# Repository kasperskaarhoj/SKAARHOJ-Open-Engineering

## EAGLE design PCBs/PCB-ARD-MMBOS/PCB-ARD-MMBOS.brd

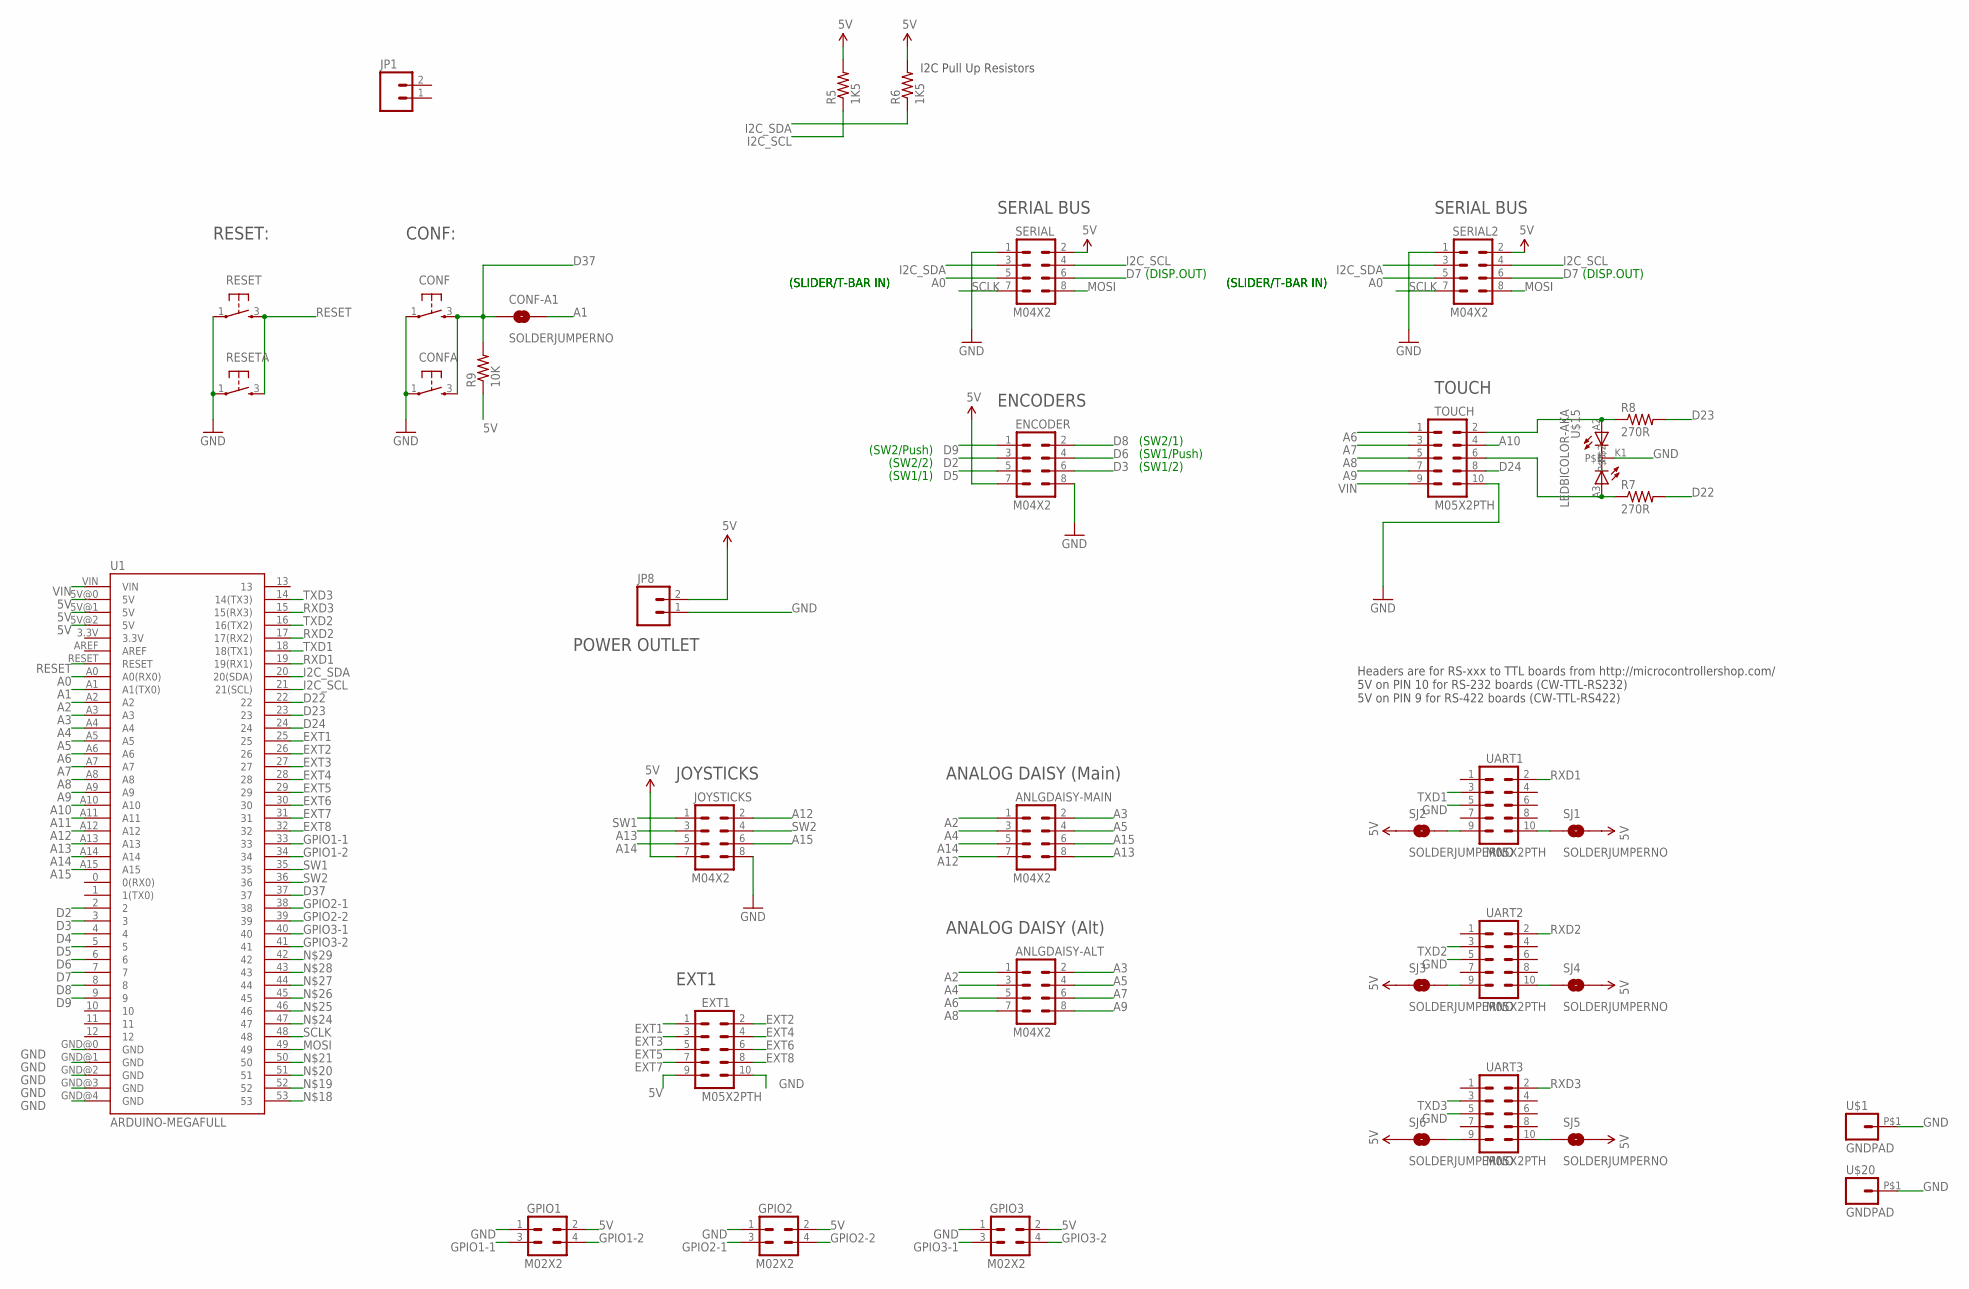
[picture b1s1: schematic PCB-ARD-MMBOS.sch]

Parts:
ANLGDAISY-ALT: M04X2; 2X4
ANLGDAISY-MAIN: M04X2; 2X4
CONF: TAC_SWITCH; PUSHBUTTON
CONF-A1: SOLDERJUMPERNO; SJ_2S-NO
CONFA: TAC_SWITCH; PUSHBUTTON
ENCODER: M04X2; 2X4
EXT1: M05X2PTH; AVR_ICSP
GPIO1, GPIO2, GPIO3: M02X2; 2X2
JOYSTICKS: M04X2; 2X4
JP1: M02PTH; 1X02
JP8: M02PTH4; 1X02_XTRA_BIG
R5, R6: 1K5; 0603-RES
R7, R8: 270R; 0603-RES
R9: 10K; 0603-RES
RESET: TAC_SWITCH; PUSHBUTTON
RESETA: TAC_SWITCH; PUSHBUTTON
SERIAL, SERIAL2: M04X2; 2X4
SJ1, SJ2, SJ3, SJ4, SJ5, SJ6: SOLDERJUMPERNO; SJ_2S-NO
TOUCH: M05X2PTH; AVR_ICSP
U1: ARDUINO-MEGAFULL; ARDUINO_MEGA
U$1, U$20: GNDPAD; 3.2MMPAD
U$15: LEDBICOLOR-AKA; LED5MM-BICOLOR
UART1, UART2, UART3: M05X2PTH; AVR_ICSP

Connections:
5V: ENCODER.7, EXT1.9, GPIO1.2, GPIO2.2, GPIO3.2, JOYSTICKS.7, JP8.2, R5.2, R6.2, R9.1, SERIAL.2, SERIAL2.2, SJ1.2, SJ2.1, SJ3.1, SJ4.2, SJ5.2, SJ6.1, U1.5V@0 (5V), U1.5V@1 (5V), U1.5V@2 (5V)
A0: SERIAL.5, SERIAL2.5, U1.A0 (A0(RX0))
A1: CONF-A1.2, U1.A1 (A1(TX0))
A2: ANLGDAISY-ALT.1, ANLGDAISY-MAIN.1, U1.A2
A3: ANLGDAISY-ALT.2, ANLGDAISY-MAIN.2, U1.A3
A4: ANLGDAISY-ALT.3, ANLGDAISY-MAIN.3, U1.A4
A5: ANLGDAISY-ALT.4, ANLGDAISY-MAIN.4, U1.A5
A6: ANLGDAISY-ALT.5, TOUCH.1, U1.A6
A7: ANLGDAISY-ALT.6, TOUCH.3, U1.A7
A8: ANLGDAISY-ALT.7, TOUCH.5, U1.A8
A9: ANLGDAISY-ALT.8, TOUCH.7, U1.A9
A10: TOUCH.4, U1.A10
A11: U1.A11
A12: ANLGDAISY-MAIN.7, JOYSTICKS.2, U1.A12
A13: ANLGDAISY-MAIN.8, JOYSTICKS.3, U1.A13
A14: ANLGDAISY-MAIN.5, JOYSTICKS.5, U1.A14
A15: ANLGDAISY-MAIN.6, JOYSTICKS.6, U1.A15
D2: ENCODER.3, U1.2
D3: ENCODER.6, U1.3
D4: U1.4
D5: ENCODER.5, U1.5
D6: ENCODER.4, U1.6
D7: SERIAL.6, SERIAL2.6, U1.7
D8: ENCODER.2, U1.8
D9: ENCODER.1, U1.9
D22: R7.2, U1.22
D23: R8.2, U1.23
D24: TOUCH.8, U1.24
D37: CONF.3, CONF-A1.1, CONFA.3, R9.2, U1.37
EXT1: EXT1.1, U1.25
EXT2: EXT1.2, U1.26
EXT3: EXT1.3, U1.27
EXT4: EXT1.4, U1.28
EXT5: EXT1.5, U1.29
EXT6: EXT1.6, U1.30
EXT7: EXT1.7, U1.31
EXT8: EXT1.8, U1.32
GND: CONF.1, CONFA.1, ENCODER.8, EXT1.10, GPIO1.1, GPIO2.1, GPIO3.1, JOYSTICKS.8, JP8.1, RESET.1, RESETA.1, SERIAL.1, SERIAL2.1, TOUCH.10, U1.GND@0 (GND), U1.GND@1 (GND), U1.GND@2 (GND), U1.GND@3 (GND), U1.GND@4 (GND), U$1.P$1, U$15.K1, U$20.P$1, UART1.5, UART2.5, UART3.5
GPIO1-1: GPIO1.3, U1.33
GPIO1-2: GPIO1.4, U1.34
GPIO2-1: GPIO2.3, U1.38
GPIO2-2: GPIO2.4, U1.39
GPIO3-1: GPIO3.3, U1.40
GPIO3-2: GPIO3.4, U1.41
I2C_SCL: R5.1, SERIAL.4, SERIAL2.4, U1.21 (21(SCL))
I2C_SDA: R6.1, SERIAL.3, SERIAL2.3, U1.20 (20(SDA))
MOSI: SERIAL.8, SERIAL2.8, U1.49
unnamed: SJ6.2, UART3.9
unnamed: SJ3.2, UART2.9
unnamed: SJ2.2, UART1.9
unnamed: SJ1.1, UART1.10
unnamed: SJ4.1, UART2.10
unnamed: SJ5.1, UART3.10
unnamed: R8.1, TOUCH.2, U$15.A2
unnamed: R7.1, TOUCH.6, U$15.A3
RESET: RESET.3, RESETA.3, U1.RESET
RXD1: U1.19 (19(RX1)), UART1.2
RXD2: U1.17 (17(RX2)), UART2.2
RXD3: U1.15 (15(RX3)), UART3.2
SCLK: SERIAL.7, SERIAL2.7, U1.48
SW1: JOYSTICKS.1, U1.35
SW2: JOYSTICKS.4, U1.36
TXD1: U1.18 (18(TX1)), UART1.3
TXD2: U1.16 (16(TX2)), UART2.3
TXD3: U1.14 (14(TX3)), UART3.3
VIN: TOUCH.9, U1.VIN

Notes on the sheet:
JOYSTICKS
EXT1
Headers are for RS-xxx to TTL boards from http://microcontrollershop.com/ 5V on PIN 10 for RS-232 boards (CW-TTL-RS232) 5V on PIN 9 for RS-422 boards (CW-TTL-RS422)
I2C Pull Up Resistors
ENCODERS
SERIAL BUS
TOUCH
(SLIDER/T-BAR IN)
(SW2/Push)
(SW2/2)
(SW1/1)
(SW2/1)
(SW1/Push)
(SW1/2)
(DISP.OUT)
RESET:
CONF:
ANALOG DAISY (Main)
ANALOG DAISY (Alt)
POWER OUTLET

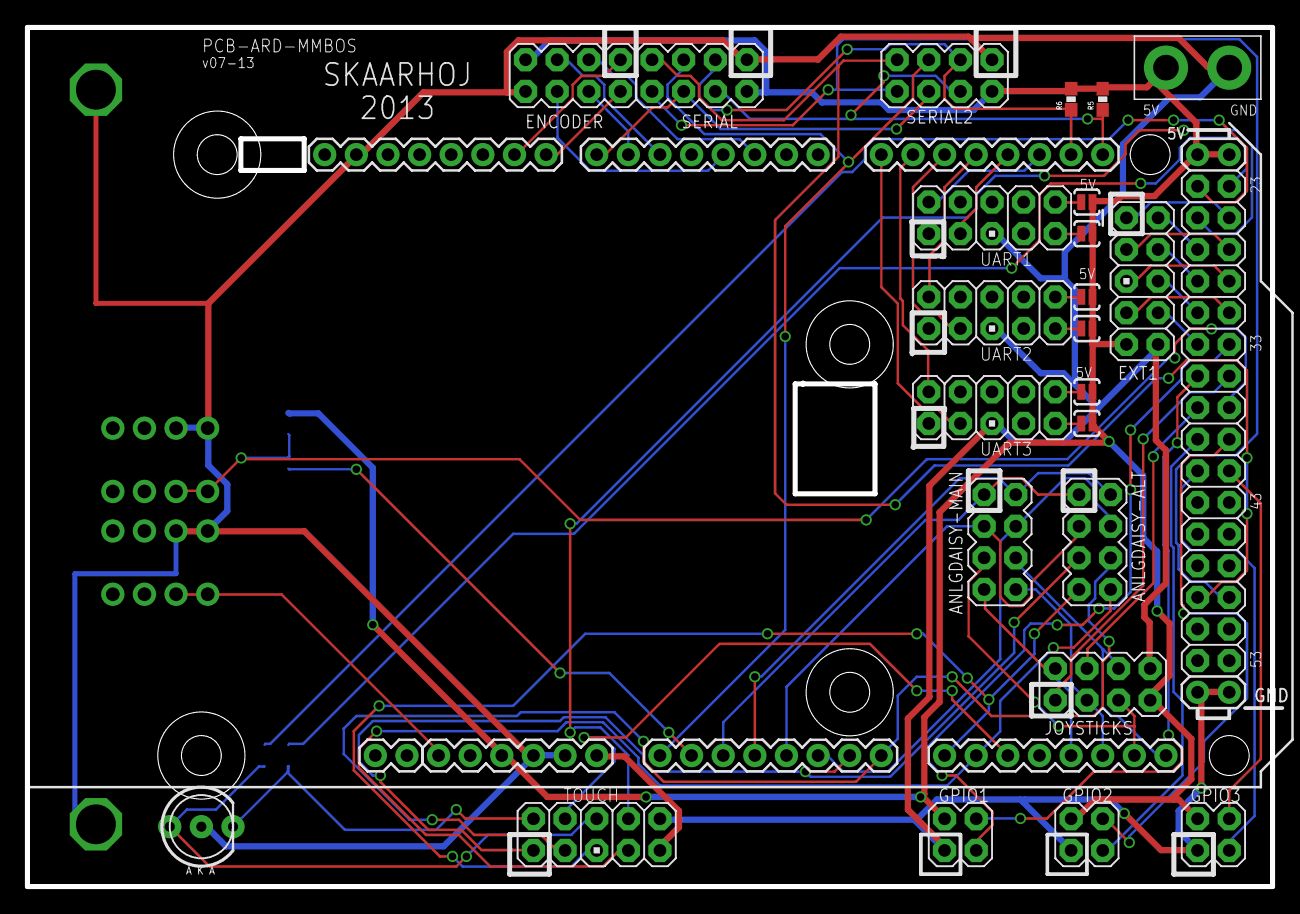
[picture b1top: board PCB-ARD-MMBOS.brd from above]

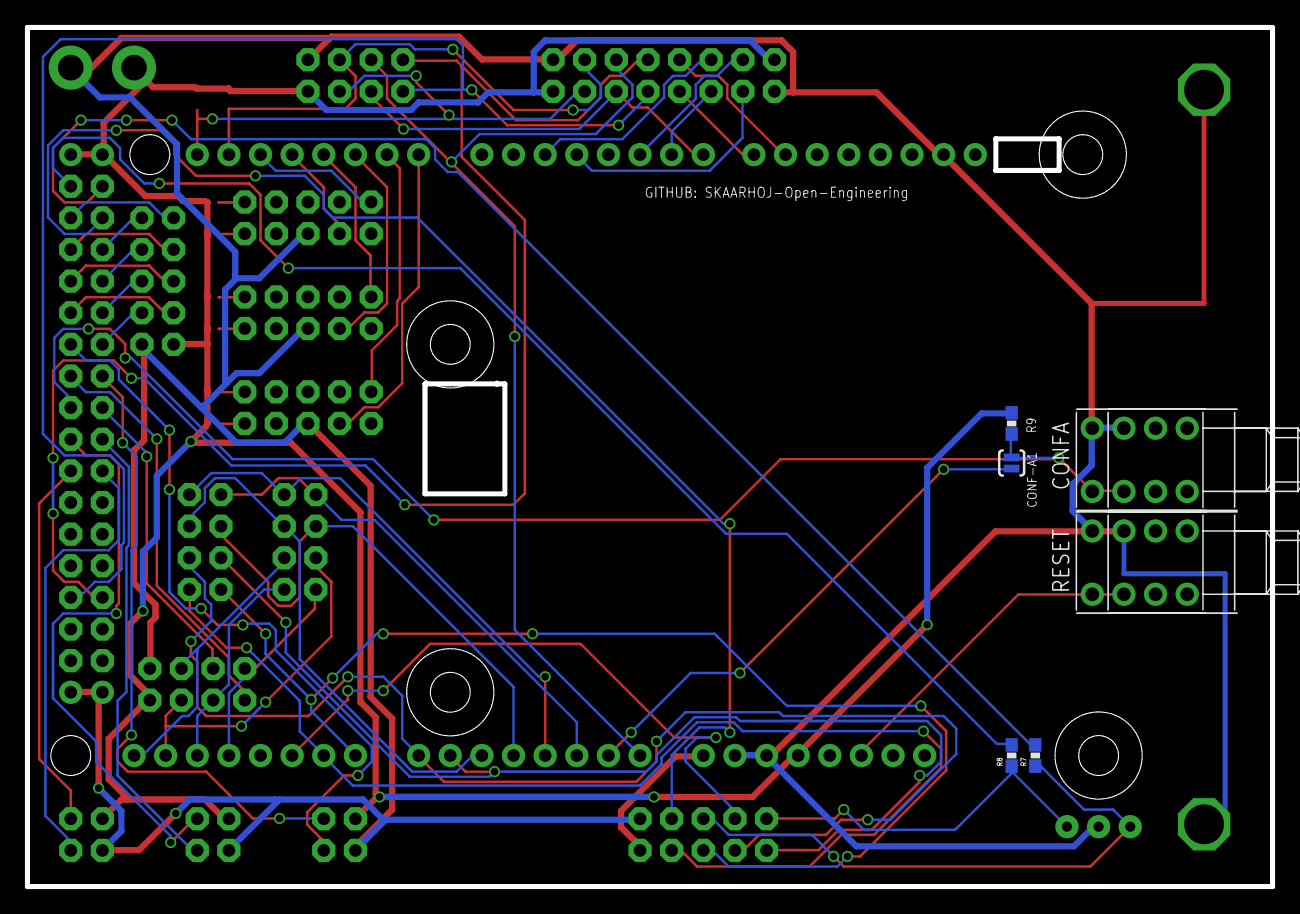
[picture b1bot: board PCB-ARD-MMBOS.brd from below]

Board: 2 copper layers, 100.0 x 69.0 mm, 36 parts (8 on the bottom side), 64 nets.

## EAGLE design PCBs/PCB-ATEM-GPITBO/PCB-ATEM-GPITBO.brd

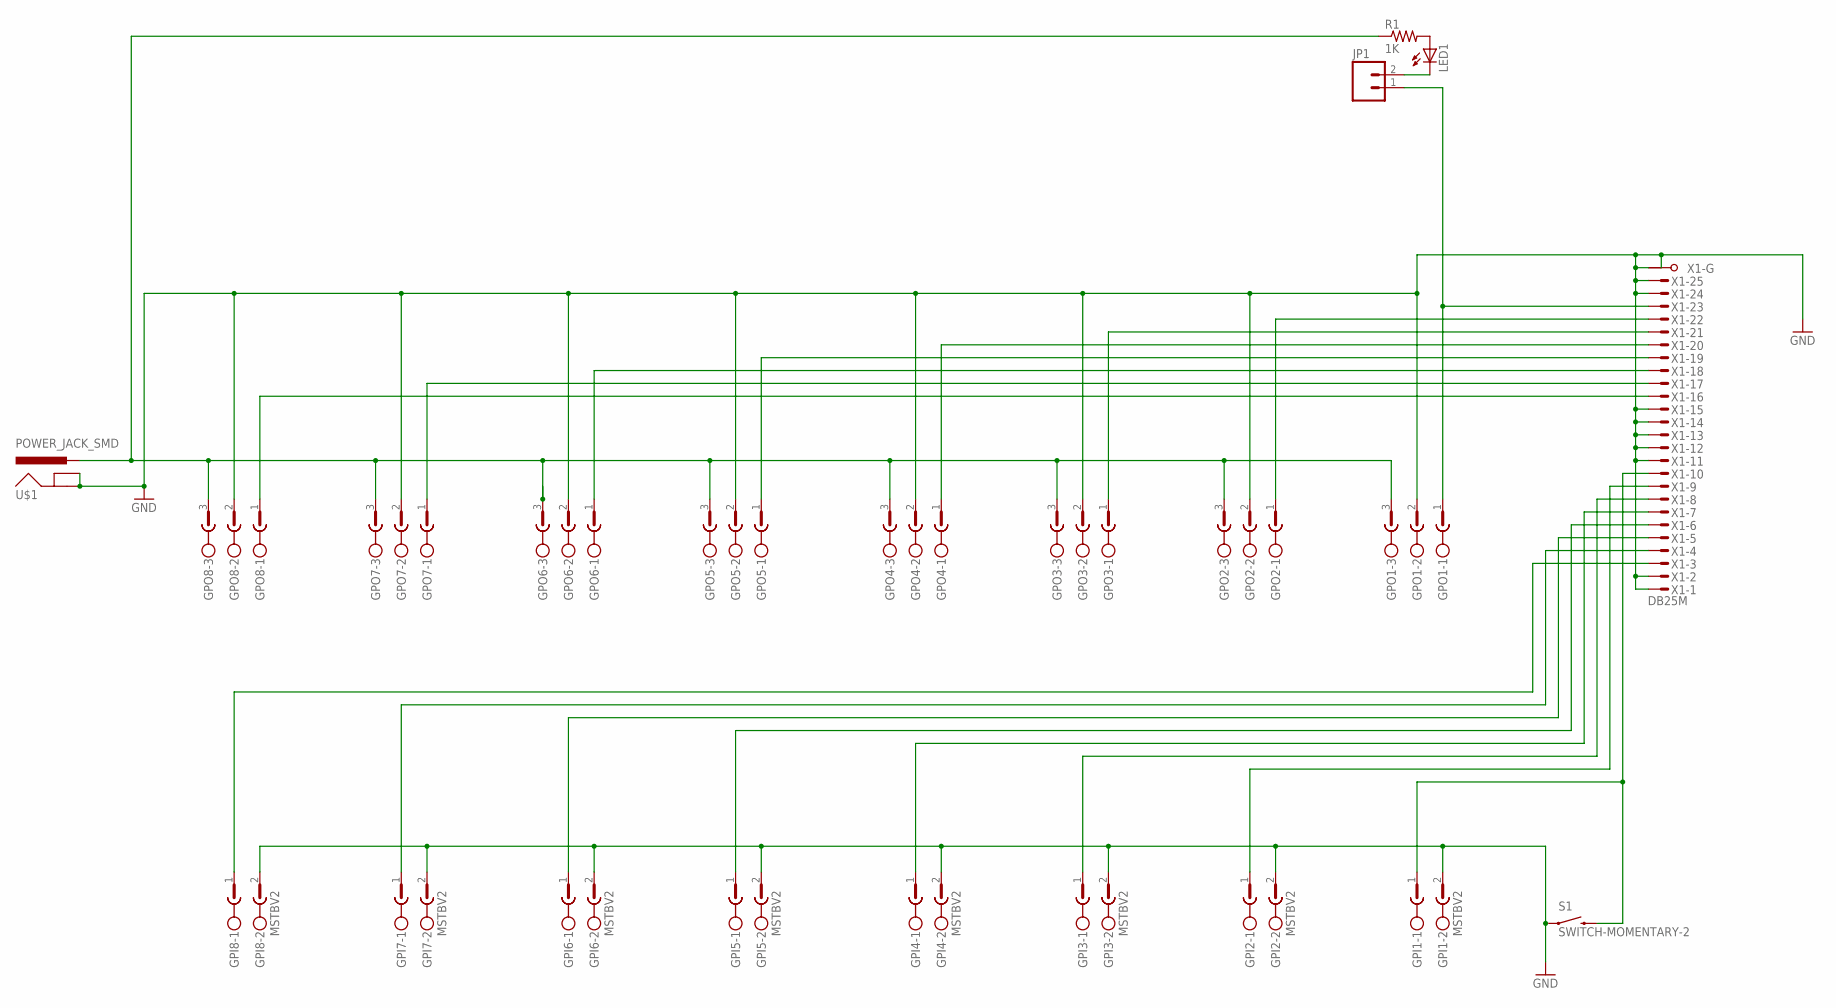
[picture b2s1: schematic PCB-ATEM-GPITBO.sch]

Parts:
GPI1, GPI2, GPI3, GPI4, GPI5, GPI6, GPI7, GPI8: MSTBV2; MPN MSTBV 2,5/2-GF-5.08
GPO1, GPO2, GPO3, GPO4, GPO5, GPO6, GPO7, GPO8: CON1; MSTBV3
JP1: M02LOCK; 1X02_LOCK
LED1: LED5MM
R1: 1K; AXIAL-0.4
S1: SWITCH-MOMENTARY-2; TACTILE_SWITCH_TALL
U$1: POWER_JACK_SMD
X1: DB25M; M25HP

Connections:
GND: GPI1.2, GPI2.2, GPI3.2, GPI4.2, GPI5.2, GPI6.2, GPI7.2, GPI8.2, GPO1.2, GPO2.2, GPO3.2, GPO4.2, GPO5.2, GPO6.2, GPO7.2, GPO8.2, S1.A2 (1), U$1.GND, U$1.SHUNT (GNDBREAK), X1.1 (M), X1.2 (M), X1.11 (M), X1.12 (M), X1.13 (M), X1.14 (M), X1.15 (M), X1.24 (M), X1.25 (M), X1.G1, X1.G2
unnamed: GPO1.1, JP1.1, X1.23 (M)
unnamed: JP1.2, LED1.K (C)
unnamed: LED1.A, R1.P$2 (2)
unnamed: GPO2.1, X1.22 (M)
unnamed: GPO3.1, X1.21 (M)
unnamed: GPO4.1, X1.20 (M)
unnamed: GPO5.1, X1.19 (M)
unnamed: GPO6.1, X1.18 (M)
unnamed: GPO7.1, X1.17 (M)
unnamed: GPO8.1, X1.16 (M)
unnamed: GPI1.1, S1.B2 (2), X1.10 (M)
unnamed: GPI5.1, X1.6 (M)
unnamed: GPI2.1, X1.9 (M)
unnamed: GPI3.1, X1.8 (M)
unnamed: GPI4.1, X1.7 (M)
unnamed: GPI6.1, X1.5 (M)
unnamed: GPI7.1, X1.4 (M)
unnamed: GPI8.1, X1.3 (M)
unnamed: GPO1.3, GPO2.3, GPO3.3, GPO4.3, GPO5.3, GPO6.3, GPO7.3, GPO8.3, R1.P$1 (1), U$1.PWR

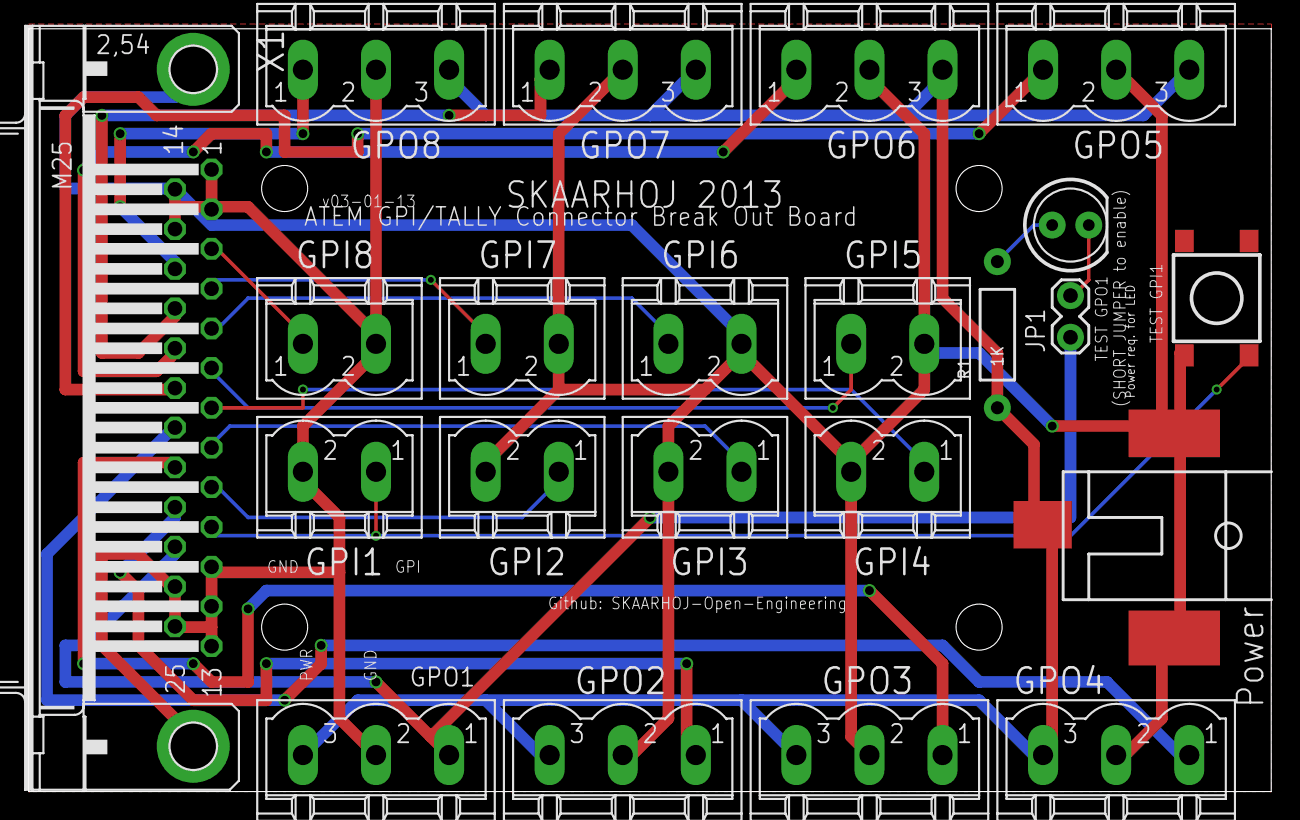
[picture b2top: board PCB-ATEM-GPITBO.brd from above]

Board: 2 copper layers, 86.3 x 53.0 mm, 22 parts (0 on the bottom side), 20 nets.

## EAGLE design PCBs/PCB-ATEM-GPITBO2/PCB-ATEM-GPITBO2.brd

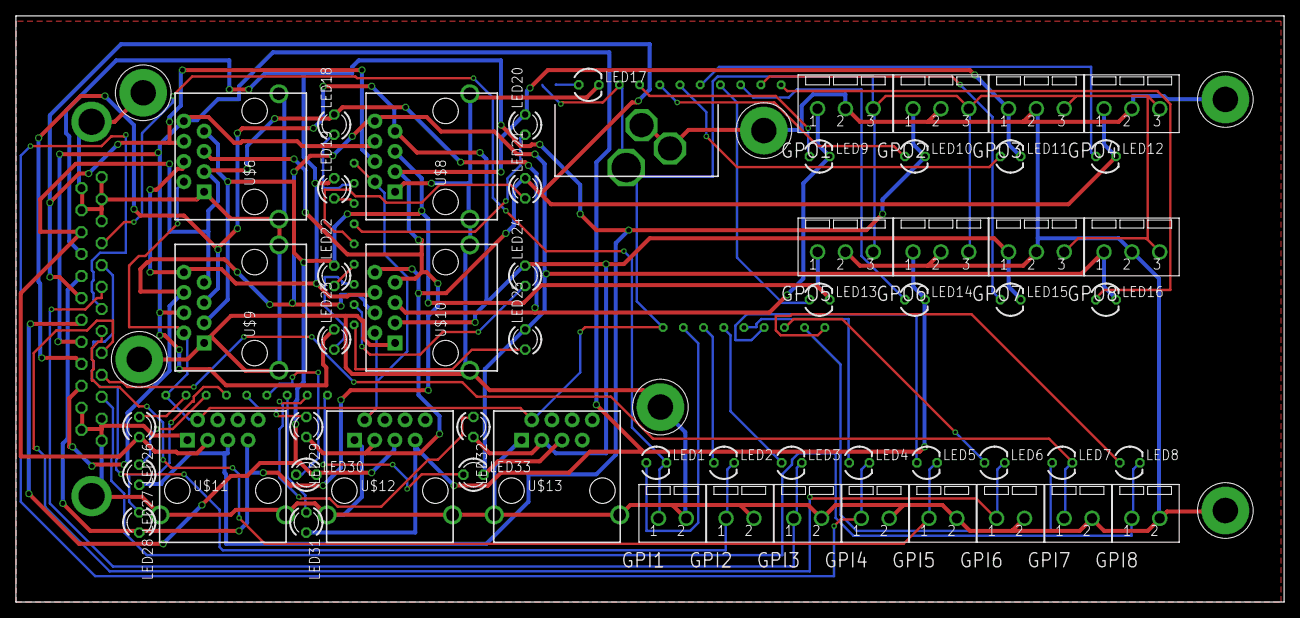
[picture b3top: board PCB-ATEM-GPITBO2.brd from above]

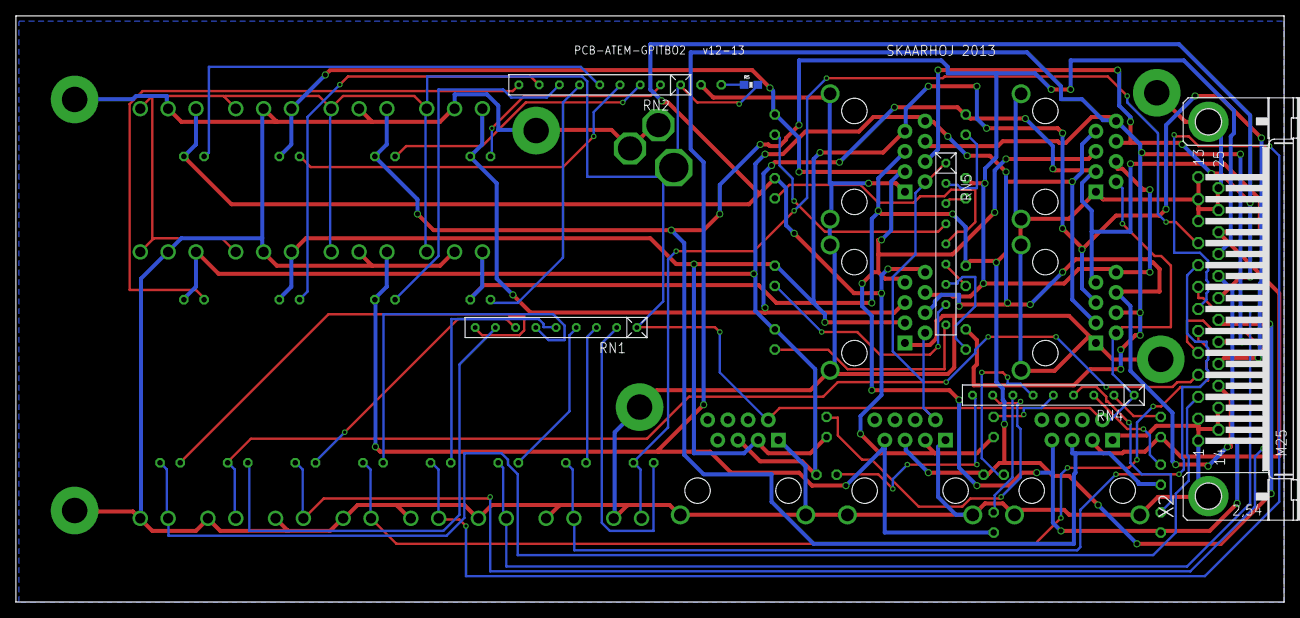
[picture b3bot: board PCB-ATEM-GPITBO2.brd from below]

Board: 2 copper layers, 159.4 x 73.7 mm, 69 parts (6 on the bottom side), 51 nets.

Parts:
GPI1, GPI2, GPI3, GPI4, GPI5, GPI6, GPI7, GPI8: MSTBV23.5MM; MSTBV2-3.5
GPO1, GPO2, GPO3, GPO4, GPO5, GPO6, GPO7, GPO8: CON1; MSTBV3-3.5
LED1, LED2, LED3, LED4, LED5, LED6, LED7, LED8, LED9, LED10, LED11, LED12, LED13, LED14, LED15, LED16, LED17: 3mm LED; LED3MM
LED18, LED19, LED20, LED21, LED22, LED23, LED24, LED25, LED26, LED27, LED28, LED29, LED30, LED31, LED32, LED33: LED3MM
R5: 0603-RES
RN1, RN2, RN4, RN5: RN-9
U$4, U$15, U$18, U$20, U$21, U$23: GNDPAD6MM; 3.2MMPAD6MM
U$5: POWER_JACKPTH_UPRIGHT; POWER_JACK_PTH_UPRIGHT
U$6, U$11: Tally 1-2-3; RJ45-8_GND_UPRIGHT
U$8, U$12: Tally 2-3-4; RJ45-8_GND_UPRIGHT
U$9, U$13: Tally 3-4-1; RJ45-8_GND_UPRIGHT
U$10: Tally 4-1-2; RJ45-8_GND_UPRIGHT
X2: DB25M; M25HP

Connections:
GND: GPI1.2, GPI2.2, GPI3.2, GPI4.2, GPI5.2, GPI6.2, GPI7.2, GPI8.2, GPO1.2, GPO2.2, GPO3.2, GPO4.2, GPO5.2, GPO6.2, GPO7.2, GPO8.2, LED17.K, U$4.P$1, U$5.GND, U$5.SHUNT, U$6.1, U$6.GND, U$6.GND1, U$8.1, U$8.GND, U$8.GND1, U$9.1, U$9.GND, U$9.GND1, U$10.1, U$10.GND, U$10.GND1, U$11.1, U$11.GND, U$11.GND1, U$12.1, U$12.GND, U$12.GND1, U$13.1, U$13.GND, U$13.GND1, U$15.P$1, U$18.P$1, U$20.P$1, U$21.P$1, U$23.P$1, X2.1, X2.2, X2.11, X2.12, X2.13, X2.14, X2.15, X2.24, X2.25, X2.G1, X2.G2
GPI1: GPI1.1, LED1.K, X2.10
GPI2: GPI2.1, LED2.K, X2.9
GPI3: GPI3.1, LED3.K, X2.8
GPI4: GPI4.1, LED4.K, X2.7
GPI5: GPI5.1, LED5.K, X2.6
GPI6: GPI6.1, LED6.K, X2.5
GPI7: GPI7.1, LED7.K, X2.4
GPI8: GPI8.1, LED8.K, X2.3
GPO1: GPO1.1, LED9.K, LED18.K, LED26.K, U$6.3, U$9.7, U$10.5, U$11.3, X2.23
GPO2: GPO2.1, LED10.K, LED19.K, LED27.K, U$6.4, U$9.8, U$10.6, U$11.5, X2.22
GPO3: GPO3.1, LED11.K, LED20.K, LED28.K, U$6.5, U$8.3, U$10.7, U$11.7, X2.21
GPO4: GPO4.1, LED12.K, LED21.K, LED29.K, U$6.6, U$8.4, U$10.8, U$12.3, X2.20
GPO5: GPO5.1, LED13.K, LED22.K, LED30.K, U$6.7, U$8.5, U$9.3, U$12.5, X2.19
GPO6: GPO6.1, LED14.K, LED23.K, LED31.K, U$6.8, U$8.6, U$9.4, U$12.7, X2.18
GPO7: GPO7.1, LED15.K, LED24.K, LED32.K, U$8.7, U$9.5, U$10.3, U$13.3, X2.17
GPO8: GPO8.1, LED16.K, LED25.K, LED33.K, U$8.8, U$9.6, U$10.4, U$13.5, X2.16
unnamed: LED1.A, RN1.2
unnamed: LED2.A, RN1.3
unnamed: LED18.A, RN5.2
unnamed: LED3.A, RN1.4
unnamed: LED19.A, RN5.3
unnamed: LED4.A, RN1.5
unnamed: LED20.A, RN5.4
unnamed: LED5.A, RN1.6
unnamed: LED6.A, RN1.7
unnamed: LED7.A, RN1.8
unnamed: LED21.A, RN5.5
unnamed: LED8.A, RN1.9
unnamed: LED9.A, RN2.2
unnamed: LED10.A, RN2.3
unnamed: LED22.A, RN5.6
unnamed: LED11.A, RN2.4
unnamed: LED12.A, RN2.5
unnamed: LED13.A, RN2.6
unnamed: LED23.A, RN5.7
unnamed: LED14.A, RN2.7
unnamed: LED15.A, RN2.8
unnamed: LED16.A, RN2.9
unnamed: LED24.A, RN5.8
unnamed: LED17.A, R5.1
unnamed: LED25.A, RN5.9
unnamed: LED26.A, RN4.2
unnamed: LED27.A, RN4.3
unnamed: LED28.A, RN4.4
unnamed: LED29.A, RN4.5
unnamed: LED30.A, RN4.6
unnamed: LED31.A, RN4.7
unnamed: LED32.A, RN4.8
unnamed: LED33.A, RN4.9
VCC: GPO1.3, GPO2.3, GPO3.3, GPO4.3, GPO5.3, GPO6.3, GPO7.3, GPO8.3, R5.2, RN1.1, RN2.1, RN4.1, RN5.1, U$5.PWR, U$6.2, U$8.2, U$9.2, U$10.2, U$11.2, U$12.2, U$13.2

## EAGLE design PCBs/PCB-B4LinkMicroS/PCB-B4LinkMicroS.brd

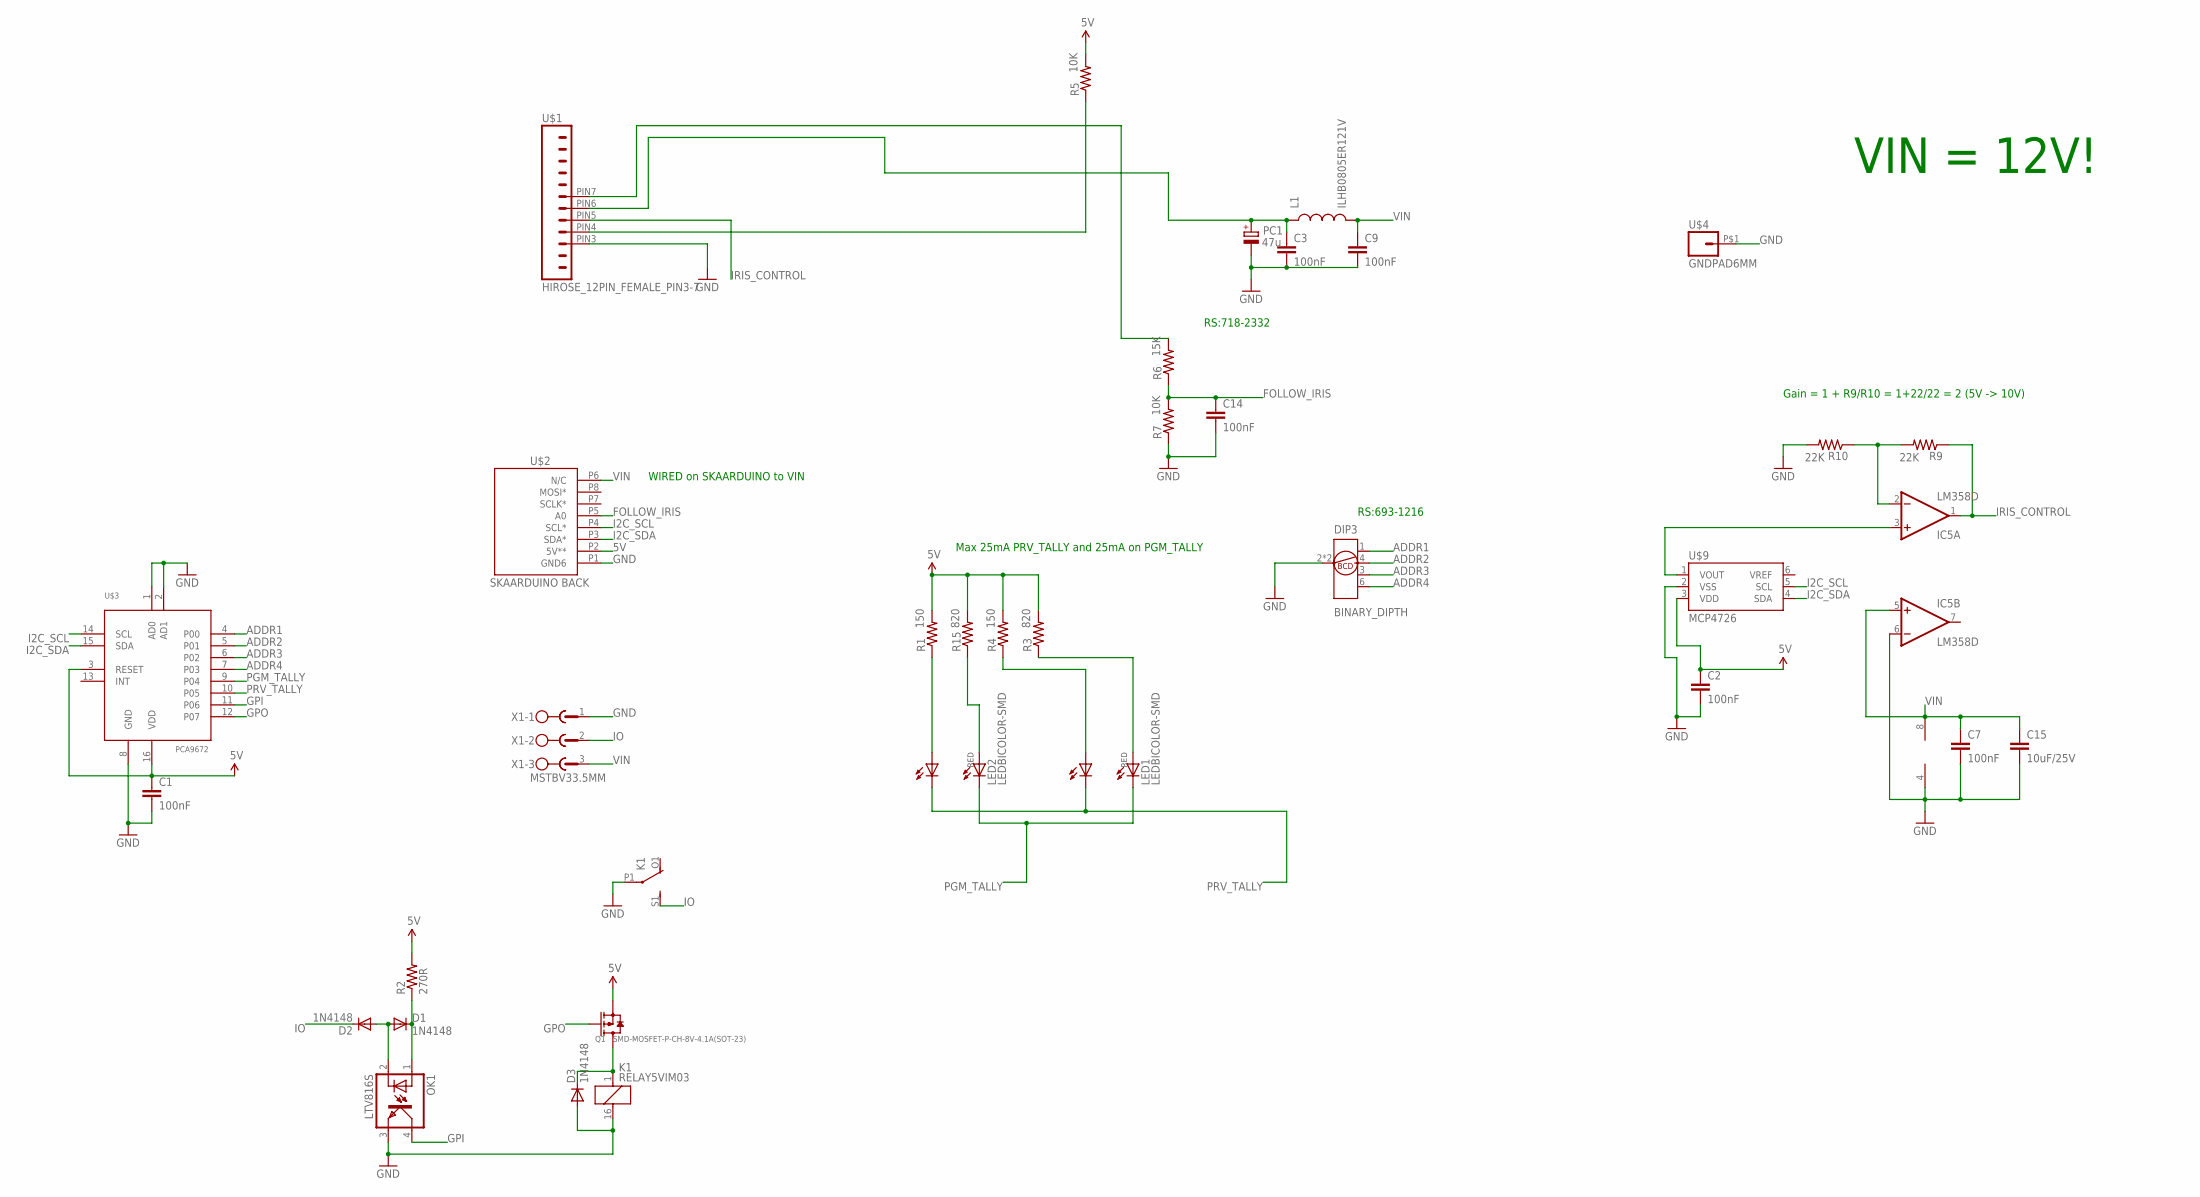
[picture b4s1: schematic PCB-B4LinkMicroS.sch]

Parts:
C1, C2, C3, C7, C9, C14: 100nF; 0603-CAP
C15: 10uF/25V; 0805
D1, D2, D3: 1N4148; SOD-323
DIP3: BINARY_DIPTH; P65TH
IC5: LM358D; SO08
K1: RELAY5VIM03; DS2Y
L1: ILHB0805ER121V; 0805
LED1, LED2: LEDBICOLOR-SMD
OK1: LTV816S; SMD4
PC1: 47u; PANASONIC_D
Q1: SMD-MOSFET-P-CH-8V-4.1A(SOT-23); SOT-23
R1, R4: 150; 0603-RES
R2: 270R; 0603-RES
R3, R15: 820; 0603-RES
R5, R7: 10K; 0603-RES
R6: 15K; 0603-RES
R9, R10: 22K; 0603-RES
U$1: HIROSE_12PIN_FEMALE_PIN3-7; HIROSE_12PIN_RECEP_LESSHOLES
U$2: SKAARDUINO_BACK_SERIAL; SKAARDUINO_BACK_PTH_SERIAL
U$3: PCA9672; TSSOP16
U$4: GNDPAD6MM; 3.2MMPAD6MM
U$9: MCP4726; SOT23-6L
X1: MSTBV33.5MM; MSTBV3-3.5

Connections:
5V: C1.1, C2.1, Q1.2 (S), R1.2, R2.2, R3.2, R4.2, R5.2, R15.2, U$2.P2 (5V**), U$3.3 (RESET), U$3.16 (VDD), U$9.3 (VDD)
ADDR1: DIP3.1, U$3.4 (P00)
ADDR2: DIP3.4 (2), U$3.5 (P01)
ADDR3: DIP3.3 (4), U$3.6 (P02)
ADDR4: DIP3.6 (8), U$3.7 (P03)
FOLLOW_IRIS: C14.1, R6.1, R7.2, U$2.P5 (A0)
GND: C1.2, C2.2, C3.2, C7.2, C9.2, C14.2, C15.2, D3.2 (A), DIP3.2 (GND), DIP3.5 (GND), IC5.4 (V-), IC5.6 (-IN), K1.16 (2), K1.P1, OK1.3 (EMIT), PC1.-, R7.1, R10.2, U$1.PIN3 (3), U$2.P1 (GND6), U$3.1 (AD0), U$3.2 (AD1), U$3.8 (GND), U$4.P$1, U$9.2 (VSS), X1.1
GPI: OK1.4 (COL), U$3.11 (P06)
GPO: Q1.1 (G), U$3.12 (P07)
I2C_SCL: U$2.P4 (SCL*), U$3.14 (SCL), U$9.5 (SCL)
I2C_SDA: U$2.P3 (SDA*), U$3.15 (SDA), U$9.4 (SDA)
IO: D2.1 (C), K1.S1 (S), X1.2
IRIS_CONTROL: IC5.1 (OUT), R9.1, U$1.PIN5 (5)
unnamed: C3.1, L1.1, PC1.+, U$1.PIN6 (6)
unnamed: LED2.P$3 (A1), R1.1
unnamed: LED2.P$1 (A), R15.1
unnamed: D1.2 (A), D2.2 (A), OK1.2 (C)
unnamed: D1.1 (C), OK1.1 (A), R2.1
unnamed: R6.2, U$1.PIN7 (7)
unnamed: LED1.P$3 (A1), R4.1
unnamed: LED1.P$1 (A), R3.1
unnamed: D3.1 (C), K1.1, Q1.3 (D)
unnamed: IC5.2 (-IN), R9.2, R10.1
unnamed: IC5.3 (+IN), U$9.1 (VOUT)
PGM_TALLY: LED1.P$2 (C), LED2.P$2 (C), U$3.9 (P04)
PRV_TALLY: LED1.P$4 (C1), LED2.P$4 (C1), U$3.10 (P05)
VIN: C7.1, C9.1, C15.1, IC5.5 (+IN), IC5.8 (V+), L1.2, U$2.P6 (N/C), X1.3
_IRIS_MANUAL: R5.1, U$1.PIN4 (4)

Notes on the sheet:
VIN = 12V!
RS:693-1216
RS:718-2332
WIRED on SKAARDUINO to VIN
Max 25mA PRV_TALLY and 25mA on PGM_TALLY
Gain = 1 + R9/R10 = 1+22/22 = 2 (5V -> 10V)

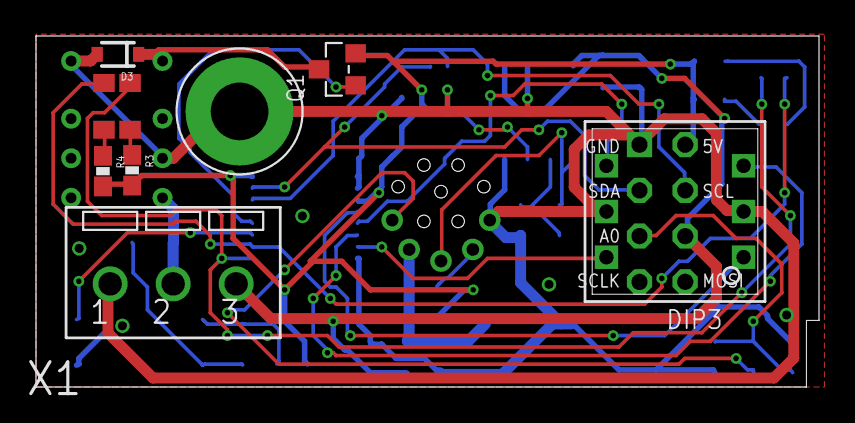
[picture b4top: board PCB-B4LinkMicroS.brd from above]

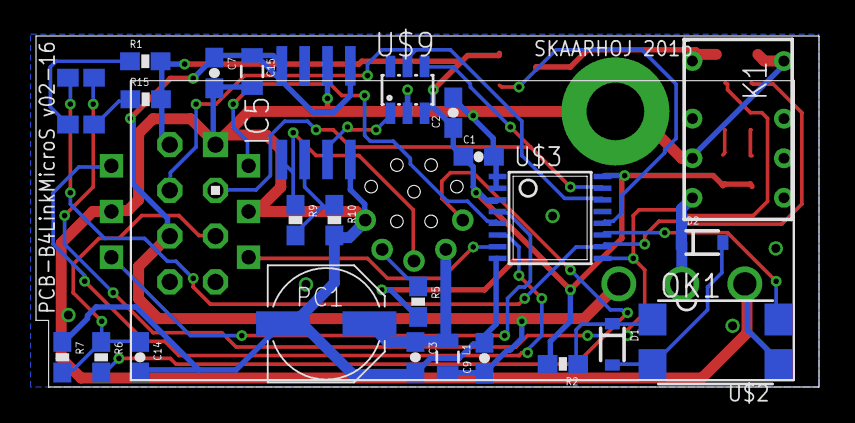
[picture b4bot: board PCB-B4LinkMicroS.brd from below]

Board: 2 copper layers, 43.5 x 19.5 mm, 35 parts (26 on the bottom side), 28 nets.

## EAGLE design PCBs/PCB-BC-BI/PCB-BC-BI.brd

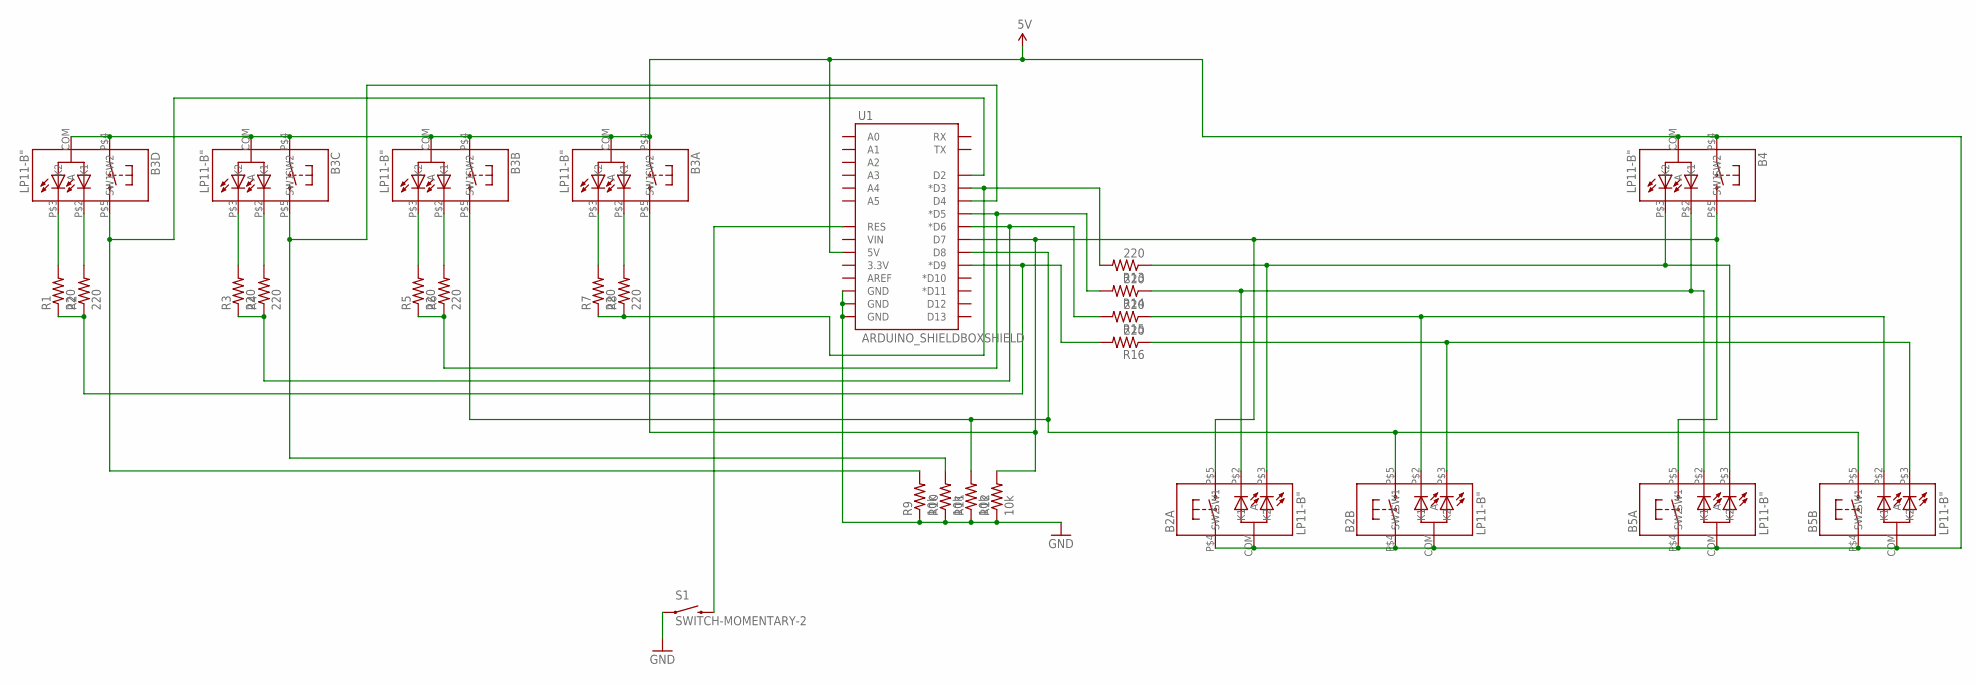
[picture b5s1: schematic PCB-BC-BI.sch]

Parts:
B2A, B2B, B3A, B3B, B3C, B3D, B4, B5A, B5B: LP11-B"; LP11
R1, R2, R3, R4, R5, R6, R7, R8, R13, R14, R15, R16: 220; 0603-RES
R9, R10, R11, R12: 10k; 0603-RES
S1: SWITCH-MOMENTARY-2; TACTILE_SWITCH_TALL
U1: ARDUINO_SHIELDBOXSHIELD; ARDUINO_BOXSHIELD

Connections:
5V: B2A.COM (A), B2A.P$4 (SW1), B2B.COM (A), B2B.P$4 (SW1), B3A.COM (A), B3A.P$4 (SW1), B3B.COM (A), B3B.P$4 (SW1), B3C.COM (A), B3C.P$4 (SW1), B3D.COM (A), B3D.P$4 (SW1), B4.COM (A), B4.P$4 (SW1), B5A.COM (A), B5A.P$4 (SW1), B5B.COM (A), B5B.P$4 (SW1), U1.5V@0 (5V)
GND: R9.1, R10.1, R11.1, R12.1, S1.A2 (1), U1.GND@0 (GND), U1.GND@1 (GND), U1.GND@4 (GND)
unnamed: B3D.P$3 (K2), R1.2
unnamed: B2A.P$3 (K2), B4.P$3 (K2), B5A.P$3 (K2), R13.1
unnamed: B3D.P$2 (K1), R2.2
unnamed: B3C.P$3 (K2), R3.2
unnamed: B3C.P$2 (K1), R4.2
unnamed: B3C.P$5 (SW2), R10.2, U1.4 (D4)
unnamed: R5.1, R6.1, R14.2, U1.5 (*D5)
unnamed: R3.1, R4.1, R15.2, U1.6 (*D6)
unnamed: R1.1, R2.1, R16.2, U1.9 (*D9)
unnamed: B2B.P$5 (SW2), B3B.P$5 (SW2), B5B.P$5 (SW2), R11.2, U1.8 (D8)
unnamed: B2A.P$2 (K1), B4.P$2 (K1), B5A.P$2 (K1), R14.1
unnamed: B2B.P$2 (K1), B5B.P$2 (K1), R15.1
unnamed: B2B.P$3 (K2), B5B.P$3 (K2), R16.1
unnamed: B2A.P$5 (SW2), B3A.P$5 (SW2), B4.P$5 (SW2), B5A.P$5 (SW2), R12.2, U1.7 (D7)
unnamed: B3B.P$3 (K2), R5.2
unnamed: B3B.P$2 (K1), R6.2
unnamed: B3A.P$3 (K2), R7.2
unnamed: B3A.P$2 (K1), R8.2
unnamed: B3D.P$5 (SW2), R9.2, U1.2 (D2)
unnamed: R7.1, R8.1, R13.2, U1.3 (*D3)
unnamed: S1.B2 (2), U1.RESET (RES)

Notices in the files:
parts and their libraries:
SparkFun: Licensing: CC v3.0 Share-Alike You are welcome to use this library for commercial purposes.
